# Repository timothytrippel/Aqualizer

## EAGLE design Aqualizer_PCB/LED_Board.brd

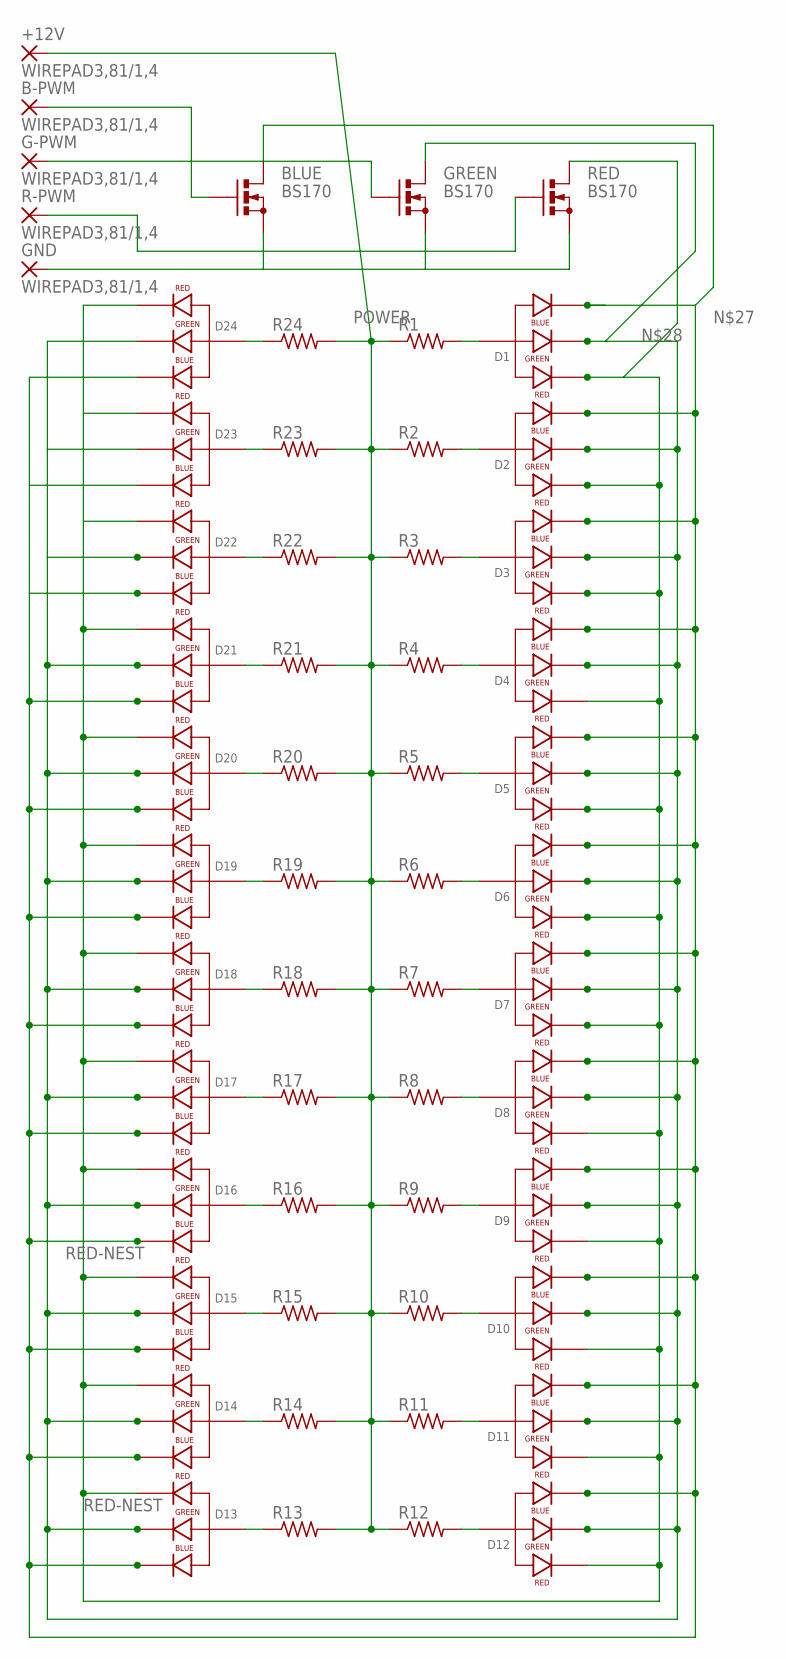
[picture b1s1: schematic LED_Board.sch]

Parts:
+12V: WIREPAD3,81/1,4; 3,81/1,4
B-PWM: WIREPAD3,81/1,4; 3,81/1,4
BLUE: BS170; SOT54E
D1, D2, D3, D4, D5, D6, D7, D8, D9, D10, D11, D12, D13, D14, D15, D16, D17, D18, D19, D20, D21, D22, D23, D24: LED-RGB-CA-THRUCLEAR; LED-RGB-THRU
G-PWM: WIREPAD3,81/1,4; 3,81/1,4
GND: WIREPAD3,81/1,4; 3,81/1,4
GREEN: BS170; SOT54E
R1, R2, R3, R4, R5, R6, R7, R8, R9, R10, R11, R12, R13, R14, R15, R16, R17, R18, R19, R20, R21, R22, R23, R24: R-US_0207/10; 0207/10
R-PWM: WIREPAD3,81/1,4; 3,81/1,4
RED: BS170; SOT54E

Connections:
unnamed: D4.2 (ANODE), R4.2
unnamed: BLUE.S, GND.1, GREEN.S, RED.S
unnamed: D24.2 (ANODE), R24.1
unnamed: D23.2 (ANODE), R23.1
unnamed: D22.2 (ANODE), R22.1
unnamed: D21.2 (ANODE), R21.1
unnamed: D20.2 (ANODE), R20.1
unnamed: D17.2 (ANODE), R17.1
unnamed: D16.2 (ANODE), R16.1
unnamed: D15.2 (ANODE), R15.1
unnamed: D14.2 (ANODE), R14.1
unnamed: D13.2 (ANODE), R13.1
unnamed: D1.2 (ANODE), R1.2
unnamed: D2.2 (ANODE), R2.2
unnamed: D3.2 (ANODE), R3.2
unnamed: D5.2 (ANODE), R5.2
unnamed: D6.2 (ANODE), R6.2
unnamed: D7.2 (ANODE), R7.2
unnamed: D8.2 (ANODE), R8.2
unnamed: D9.2 (ANODE), R9.2
unnamed: D10.2 (ANODE), R10.2
unnamed: D12.2 (ANODE), R12.2
unnamed: D11.2 (ANODE), R11.2
unnamed: BLUE.D, D1.4 (BLUE_CATHODE), D2.4 (BLUE_CATHODE), D3.4 (BLUE_CATHODE), D4.4 (BLUE_CATHODE), D5.4 (BLUE_CATHODE), D6.4 (BLUE_CATHODE), D7.4 (BLUE_CATHODE), D8.4 (BLUE_CATHODE), D9.4 (BLUE_CATHODE), D10.4 (BLUE_CATHODE), D11.4 (BLUE_CATHODE), D12.4 (BLUE_CATHODE), D13.4 (BLUE_CATHODE), D14.4 (BLUE_CATHODE), D15.4 (BLUE_CATHODE), D16.4 (BLUE_CATHODE), D17.4 (BLUE_CATHODE), D18.4 (BLUE_CATHODE), D19.4 (BLUE_CATHODE), D20.4 (BLUE_CATHODE), D21.4 (BLUE_CATHODE), D22.4 (BLUE_CATHODE), D23.4 (BLUE_CATHODE), D24.4 (BLUE_CATHODE)
unnamed: D1.3 (GREEN_CATHODE), D2.3 (GREEN_CATHODE), D3.3 (GREEN_CATHODE), D4.3 (GREEN_CATHODE), D5.3 (GREEN_CATHODE), D6.3 (GREEN_CATHODE), D7.3 (GREEN_CATHODE), D8.3 (GREEN_CATHODE), D9.3 (GREEN_CATHODE), D10.3 (GREEN_CATHODE), D11.3 (GREEN_CATHODE), D12.3 (GREEN_CATHODE), D13.3 (GREEN_CATHODE), D14.3 (GREEN_CATHODE), D15.3 (GREEN_CATHODE), D16.3 (GREEN_CATHODE), D17.3 (GREEN_CATHODE), D18.3 (GREEN_CATHODE), D19.3 (GREEN_CATHODE), D20.3 (GREEN_CATHODE), D21.3 (GREEN_CATHODE), D22.3 (GREEN_CATHODE), D23.3 (GREEN_CATHODE), D24.3 (GREEN_CATHODE), GREEN.D
unnamed: R-PWM.1, RED.G
unnamed: G-PWM.1, GREEN.G
unnamed: B-PWM.1, BLUE.G
unnamed: D18.2 (ANODE), R18.1
unnamed: D19.2 (ANODE), R19.1
POWER: +12V.1, R1.1, R2.1, R3.1, R4.1, R5.1, R6.1, R7.1, R8.1, R9.1, R10.1, R11.1, R12.1, R13.2, R14.2, R15.2, R16.2, R17.2, R18.2, R19.2, R20.2, R21.2, R22.2, R23.2, R24.2
RED-NEST: D1.1 (RED_CATHODE), D2.1 (RED_CATHODE), D3.1 (RED_CATHODE), D4.1 (RED_CATHODE), D5.1 (RED_CATHODE), D6.1 (RED_CATHODE), D7.1 (RED_CATHODE), D8.1 (RED_CATHODE), D9.1 (RED_CATHODE), D10.1 (RED_CATHODE), D11.1 (RED_CATHODE), D12.1 (RED_CATHODE), D13.1 (RED_CATHODE), D14.1 (RED_CATHODE), D15.1 (RED_CATHODE), D16.1 (RED_CATHODE), D17.1 (RED_CATHODE), D18.1 (RED_CATHODE), D19.1 (RED_CATHODE), D20.1 (RED_CATHODE), D21.1 (RED_CATHODE), D22.1 (RED_CATHODE), D23.1 (RED_CATHODE), D24.1 (RED_CATHODE), RED.D

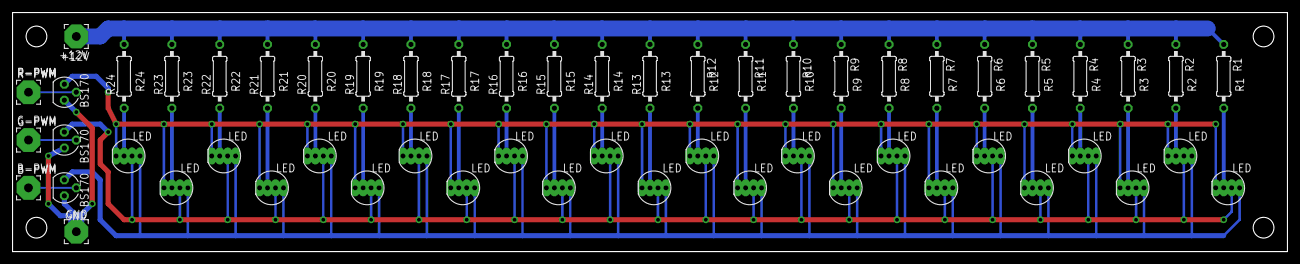
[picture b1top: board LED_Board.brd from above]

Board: 2 copper layers, 203.2 x 38.1 mm, 60 parts (0 on the bottom side), 32 nets.

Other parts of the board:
U$1, U$2, U$3, U$4: STAND-OFF

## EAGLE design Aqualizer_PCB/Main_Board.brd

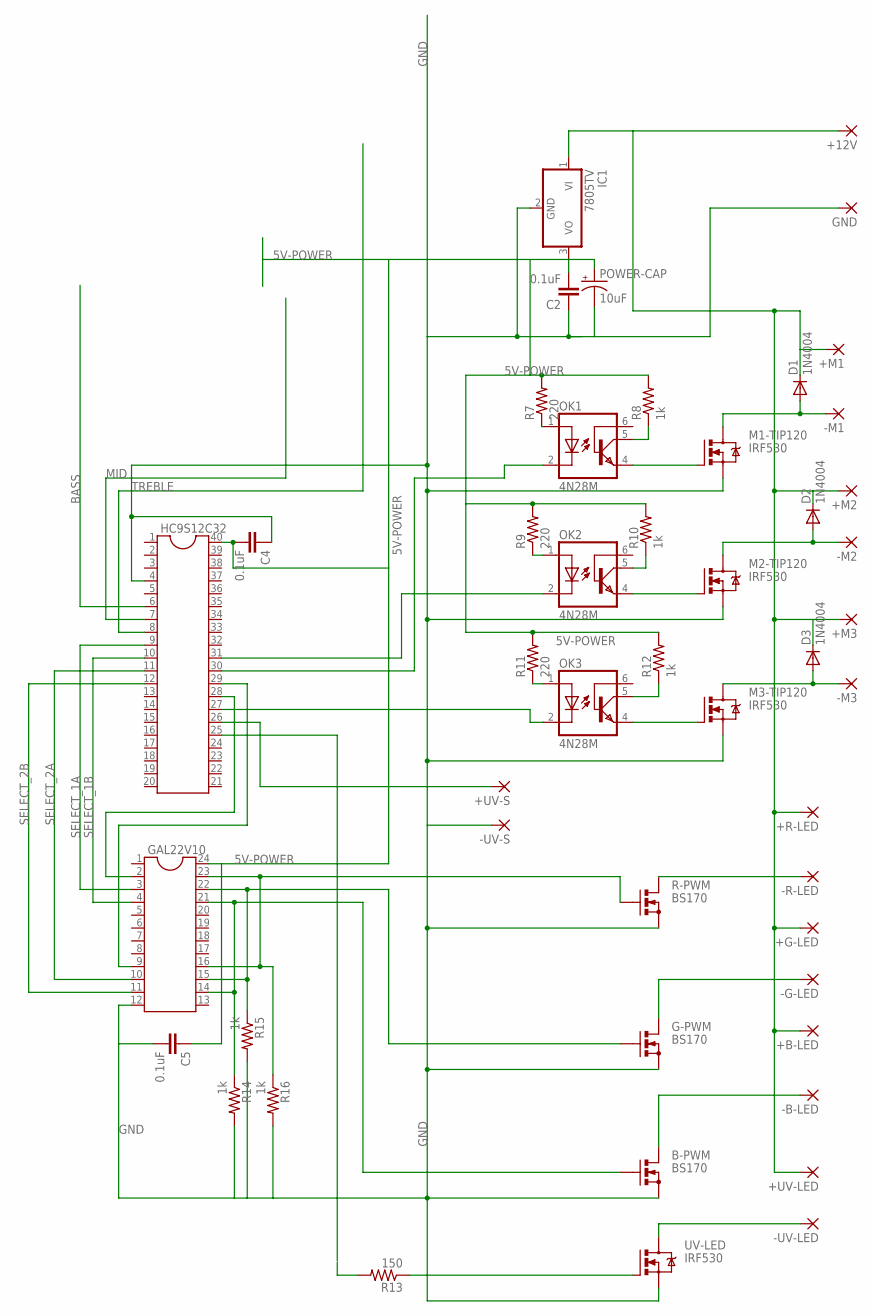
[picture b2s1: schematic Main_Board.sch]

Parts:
+12V: 3,81/1,4
+B-LED: 3,81/1,4
+G-LED: 3,81/1,4
+M1, +M2, +M3: 3,81/1,4
+R-LED: 3,81/1,4
+UV-LED: 3,81/1,4
+UV-S: 3,81/1,4
-B-LED: 3,81/1,4
-G-LED: 3,81/1,4
-M1, -M2, -M3: 3,81/1,4
-R-LED: 3,81/1,4
-UV-LED: 3,81/1,4
-UV-S: 3,81/1,4
B-PWM: BS170; SOT54E
C2, C4, C5: 0.1uF; C7.5B6
D1, D2, D3: 1N4004; DO41-10
G-PWM: BS170; SOT54E
GAL22V10: DIL24-3
GND: 3,81/1,4
HC9S12C32: DIL40
IC1: 7805TV; TO220V
M1-TIP120, M2-TIP120, M3-TIP120: IRF530; TO220BV
OK1, OK2, OK3: 4N28M; DIL06
POWER-CAP: 10uF; TT5D10
R7, R9, R11: 220; V234/12
R8, R10, R12, R14, R15, R16: 1k; V234/12
R13: 150; V234/12
R-PWM: BS170; SOT54E
UV-LED: IRF530; TO220BV

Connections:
5V-POWER: C2.2, C4.2, C5.1, GAL22V10.24, HC9S12C32.40, IC1.3 (VO), POWER-CAP.+, R7.2, R8.2, R9.2, R10.2, R11.2, R12.2
12V-POWER: +12V.1, +B-LED.1, +G-LED.1, +M1.1, +M2.1, +M3.1, +R-LED.1, +UV-LED.1, D1.C, D2.C, D3.C, IC1.1 (VI)
B-CHANNEL: B-PWM.G, GAL22V10.14, GAL22V10.21, R14.1
B-PWM: -B-LED.1, B-PWM.D
BASS: HC9S12C32.6
G-CHANNEL: G-PWM.G, GAL22V10.15, GAL22V10.22, R15.1
GND: -UV-S.1, B-PWM.S, C2.1, C4.1, C5.2, G-PWM.S, GAL22V10.12, GND.1, HC9S12C32.4, IC1.2 (GND), M1-TIP120.S, M2-TIP120.S, M3-TIP120.S, POWER-CAP.-, R14.2, R15.2, R16.2, R-PWM.S, UV-LED.S
LED1-PWM: GAL22V10.2, HC9S12C32.28
LED2-PWM: GAL22V10.9, HC9S12C32.29
M1-PWM: HC9S12C32.30, OK1.2 (C)
M2-PWM: HC9S12C32.31, OK2.2 (C)
M3-PWM: HC9S12C32.27, OK3.2 (C)
MID: HC9S12C32.7
unnamed: -UV-LED.1, UV-LED.D
unnamed: R13.1, UV-LED.G
unnamed: -G-LED.1, G-PWM.D
unnamed: -R-LED.1, R-PWM.D
unnamed: M3-TIP120.G, OK3.4 (EMI)
unnamed: +UV-S.1, HC9S12C32.26
unnamed: M2-TIP120.G, OK2.4 (EMI)
unnamed: OK2.5 (COL), R10.1
unnamed: OK1.5 (COL), R8.1
unnamed: M1-TIP120.G, OK1.4 (EMI)
unnamed: -M1.1, D1.A, M1-TIP120.D
unnamed: -M2.1, D2.A, M2-TIP120.D
unnamed: OK3.5 (COL), R12.1
unnamed: -M3.1, D3.A, M3-TIP120.D
unnamed: OK2.1 (A), R9.1
unnamed: OK1.1 (A), R7.1
unnamed: OK3.1 (A), R11.1
R-CHANNEL: GAL22V10.16, GAL22V10.23, R16.1, R-PWM.G
SELECT_1A: GAL22V10.3, HC9S12C32.9
SELECT_1B: GAL22V10.4, HC9S12C32.10
SELECT_2A: GAL22V10.10, HC9S12C32.11
SELECT_2B: GAL22V10.11, HC9S12C32.12
TREBLE: HC9S12C32.8

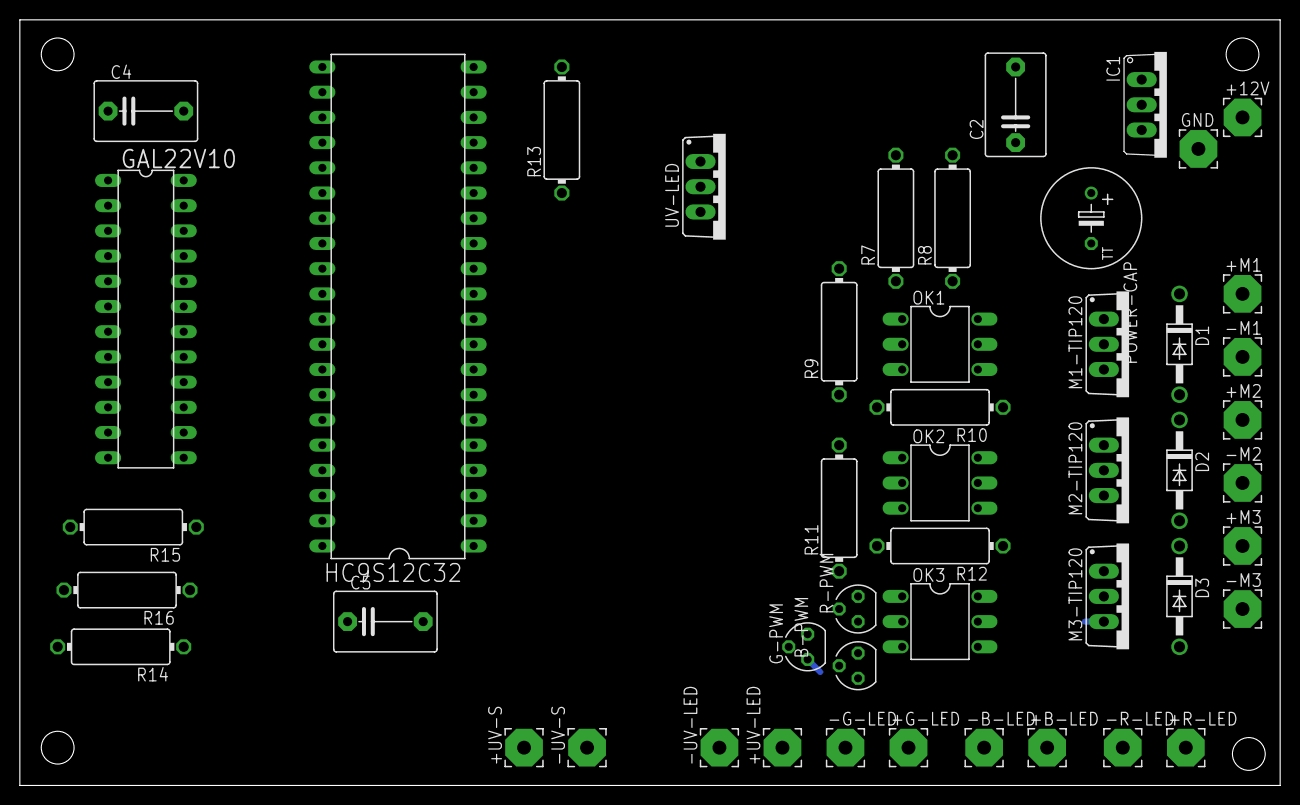
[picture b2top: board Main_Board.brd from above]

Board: 2 copper layers, 127.0 x 77.1 mm, 52 parts (0 on the bottom side), 33 nets.

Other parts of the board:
U$1, U$2, U$3, U$4: STAND-OFF

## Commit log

2014-08-19 Adding all PCB files
    adding PCB files from project

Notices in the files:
parts and their libraries:
SparkFun-LED: Licensing: CC v3.0 Share-Alike You are welcome to use this library for commercial purposes.
